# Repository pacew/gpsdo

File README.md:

<!-- -*- mode:gfm -*- -->

Documentation: https://pacew.github.io/gpsdo/

Schematic [PDF](schematic.pdf)

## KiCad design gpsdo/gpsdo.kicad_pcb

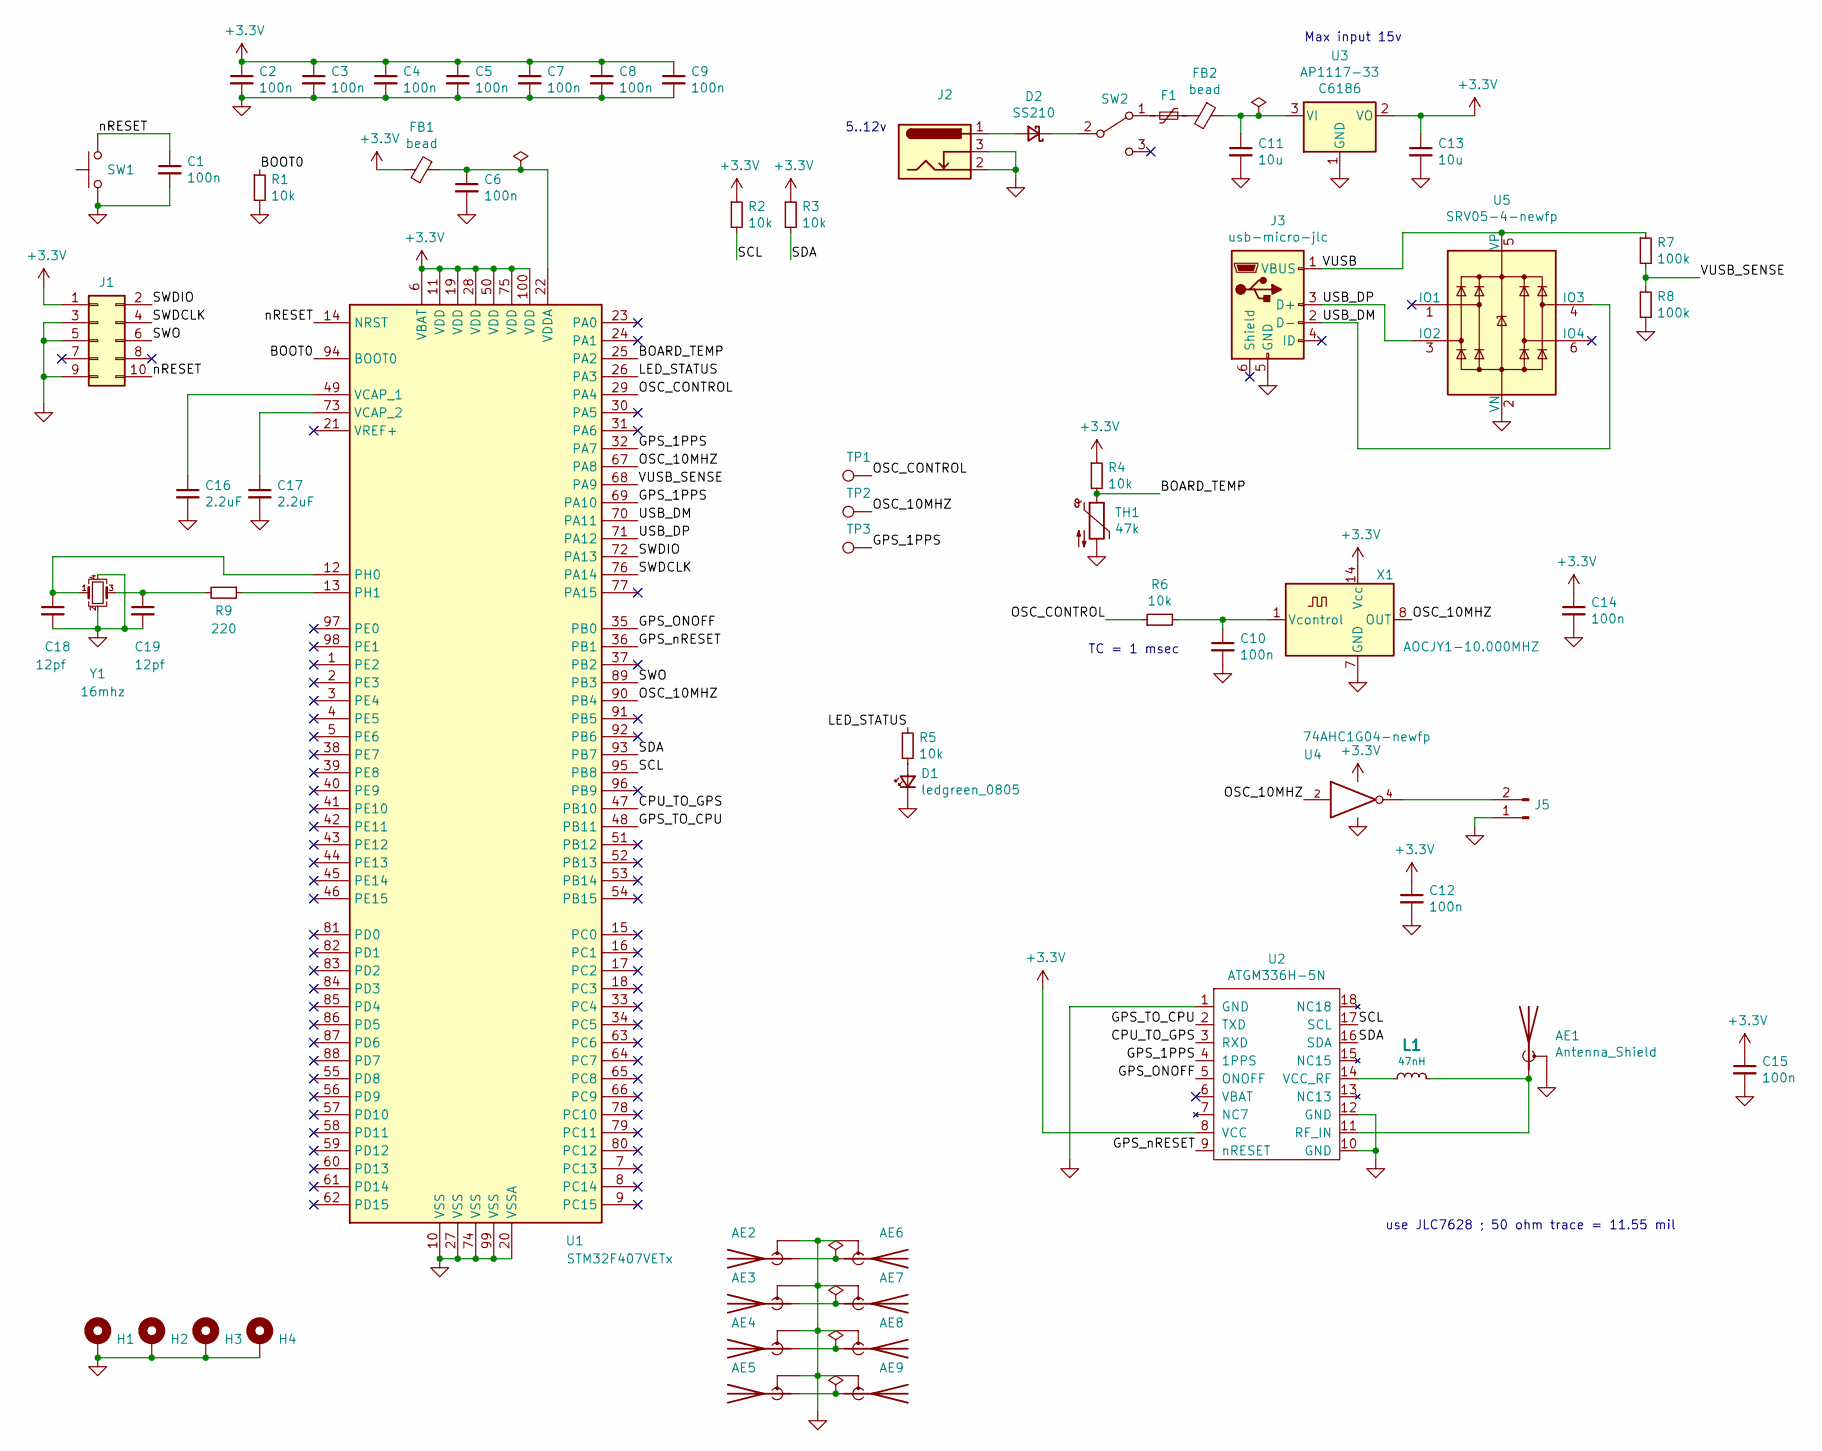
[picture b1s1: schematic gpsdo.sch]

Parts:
AE1, AE2, AE3, AE4, AE5, AE6, AE7, AE8, AE9: Antenna_Shield; sma
C1, C2, C3, C4, C5, C6, C7, C8, C9, C10, C12, C14, C15: 100n; C_0402_1005Metric; LCSC C1525
C11, C13: 10u; C_0402_1005Metric; LCSC C15525
C16, C17: 2.2uF; C_0603_1608Metric; LCSC C23630
C18, C19: 12pf; C_0402_1005Metric; LCSC C1547
D1: ledgreen_0805; LED_0805_2012Metric; LCSC C2297
D2: SS210; D_SMA; LCSC C14996
F1: fuse-250mA; Fuse_1206_3216Metric; LCSC C70068
FB1, FB2: bead; L_0805_2012Metric; LCSC C1015
H1, H2, H3, H4: MountingHole_Pad; MountingHole_3.2mm_M3_Pad
J1: Conn_02x05_Odd_Even; PinHeader_2x05_P1.27mm_Vertical
J2: Barrel_Jack_Switch; BarrelJack_Horizontal
J3: usb-micro-jlc; LCSC C404969
J5: Conn_01x02_Male; PinHeader_1x02_P2.54mm_Vertical
L1: 47nH; L_0603_1608Metric; LCSC C29683
R1, R2, R3, R4, R5, R6: 10k; R_0402_1005Metric; LCSC C25744
R7, R8: 100k; R_0402_1005Metric; LCSC C25741
R9: 220; R_0402_1005Metric; LCSC C25091
SW1: pushbutton_switch; SW_PUSH_6mm
SW2: SW_SPDT; Switch_Toggle_ATE1D-2M3-10-Z
TH1: 47k; R_0603_1608Metric; LCSC C86142
TP1, TP2, TP3: TestPoint; TestPoint_Pad_D1.0mm
U1: STM32F407VETx; LQFP-100_14x14mm_P0.5mm; lcsc C28730
U2: ATGM336H-5N; module18_9.7x10.1mm_P1.1mm; LCSC C90770
U3: AP1117-33; SOT-223-3_TabPin2; LCSC C6186
U4: 74AHC1G04-newfp; SOT-70-dck; LCSC C7466
U5: SRV05-4-newfp; SOT-23-6L-srv05; LCSC C85364
X1: AOCJY1-10.000MHZ; Oscillator_DIP-14
Y1: 16mhz; Crystal_SMD_3225-4Pin_3.2x2.5mm; LCSC C13738

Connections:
+3V3: C2.1, C3.1, C4.1, C5.1, C7.1, C8.1, C9.1, C12.1, C13.1, C14.1, C15.1, FB1.1, J1.1, R2.1, R3.1, R4.1, U1.6 (VBAT), U1.11 (VDD), U1.19 (VDD), U1.28 (VDD), U1.50 (VDD), U1.75 (VDD), U1.100 (VDD), U2.8 (VCC), U3.2 (VO), U4.5 (VCC), X1.14 (Vcc)
/BOARD_TEMP: R4.2, TH1.1, U1.25 (PA2)
/BOOT0: R1.1, U1.94 (BOOT0)
/CPU_TO_GPS: U1.47 (PB10), U2.3 (RXD)
/GPS_1PPS: TP3.1, U1.32 (PA7), U1.69 (PA10), U2.4 (1PPS)
/GPS_ONOFF: U1.35 (PB0), U2.5 (ONOFF)
/GPS_TO_CPU: U1.48 (PB11), U2.2 (TXD)
/GPS_nRESET: U1.36 (PB1), U2.9 (nRESET)
/LED_STATUS: R5.1, U1.26 (PA3)
/OSC_10MHZ: TP2.1, U1.67 (PA8), U1.90 (PB4), U4.2, X1.8 (OUT)
/OSC_CONTROL: R6.1, TP1.1, U1.29 (PA4)
/SCL: R2.2, U1.95 (PB8), U2.17 (SCL)
/SDA: R3.2, U1.93 (PB7), U2.16 (SDA)
/SWDCLK: J1.4, U1.76 (PA14)
/SWDIO: J1.2, U1.72 (PA13)
/SWO: J1.6, U1.89 (PB3)
/USB_DM: J3.2 (D-), U1.70 (PA11), U5.4 (IO3)
/USB_DP: J3.3 (D+), U1.71 (PA12), U5.3 (IO2)
/VUSB: J3.1 (VBUS), R7.1, U5.5 (VP)
/VUSB_SENSE: R7.2, R8.1, U1.68 (PA9)
/nRESET: C1.1, J1.10, SW1.2, U1.14 (NRST)
GND: AE1.2 (Shield), AE2.2 (Shield), AE3.2 (Shield), AE4.2 (Shield), AE5.2 (Shield), AE6.2 (Shield), AE7.2 (Shield), AE8.2 (Shield), AE9.2 (Shield), C1.2, C2.2, C3.2, C4.2, C5.2, C6.2, C7.2, C8.2, C9.2, C10.2, C11.2, C12.2, C13.2, C14.2, C15.2, C16.2, C17.2, C18.2, C19.2, D1.1 (K), H1.1, H2.1, H3.1, H4.1, J1.3, J1.5, J1.9, J2.2, J2.3, J3.5 (GND), J5.1, R1.2, R8.2, SW1.1, TH1.2, U1.10 (VSS), U1.20 (VSSA), U1.27 (VSS), U1.74 (VSS), U1.99 (VSS), U2.1 (GND), U2.10 (GND), U2.12 (GND), U3.1 (GND), U4.3 (GND), U5.2 (VN), X1.7 (GND), Y1.2, Y1.4
unnamed: AE1.1 (A), L1.2, U2.11 (RF_IN)
unnamed: AE2.1 (A), AE6.1 (A)
unnamed: AE3.1 (A), AE7.1 (A)
unnamed: AE4.1 (A), AE8.1 (A)
unnamed: AE5.1 (A), AE9.1 (A)
unnamed: C6.1, FB1.2, U1.22 (VDDA)
unnamed: C10.1, R6.2, X1.1 (Vcontrol)
unnamed: C11.1, FB2.1, U3.3 (VI)
unnamed: C16.1, U1.49 (VCAP_1)
unnamed: C17.1, U1.73 (VCAP_2)
unnamed: C18.1, U1.12 (PH0), Y1.1
unnamed: C19.1, R9.2, Y1.3
unnamed: D1.2 (A), R5.2
unnamed: D2.1 (K), SW2.2 (B)
unnamed: D2.2 (A), J2.1
unnamed: F1.1, FB2.2
unnamed: F1.2, SW2.1 (A)
unnamed: J5.2, U4.4
unnamed: L1.1, U2.14 (VCC_RF)
unnamed: R9.1, U1.13 (PH1)

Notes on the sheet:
TC = 1 msec
5..12v
Max input 15v
use JLC7628 ; 50 ohm trace = 11.55 mil

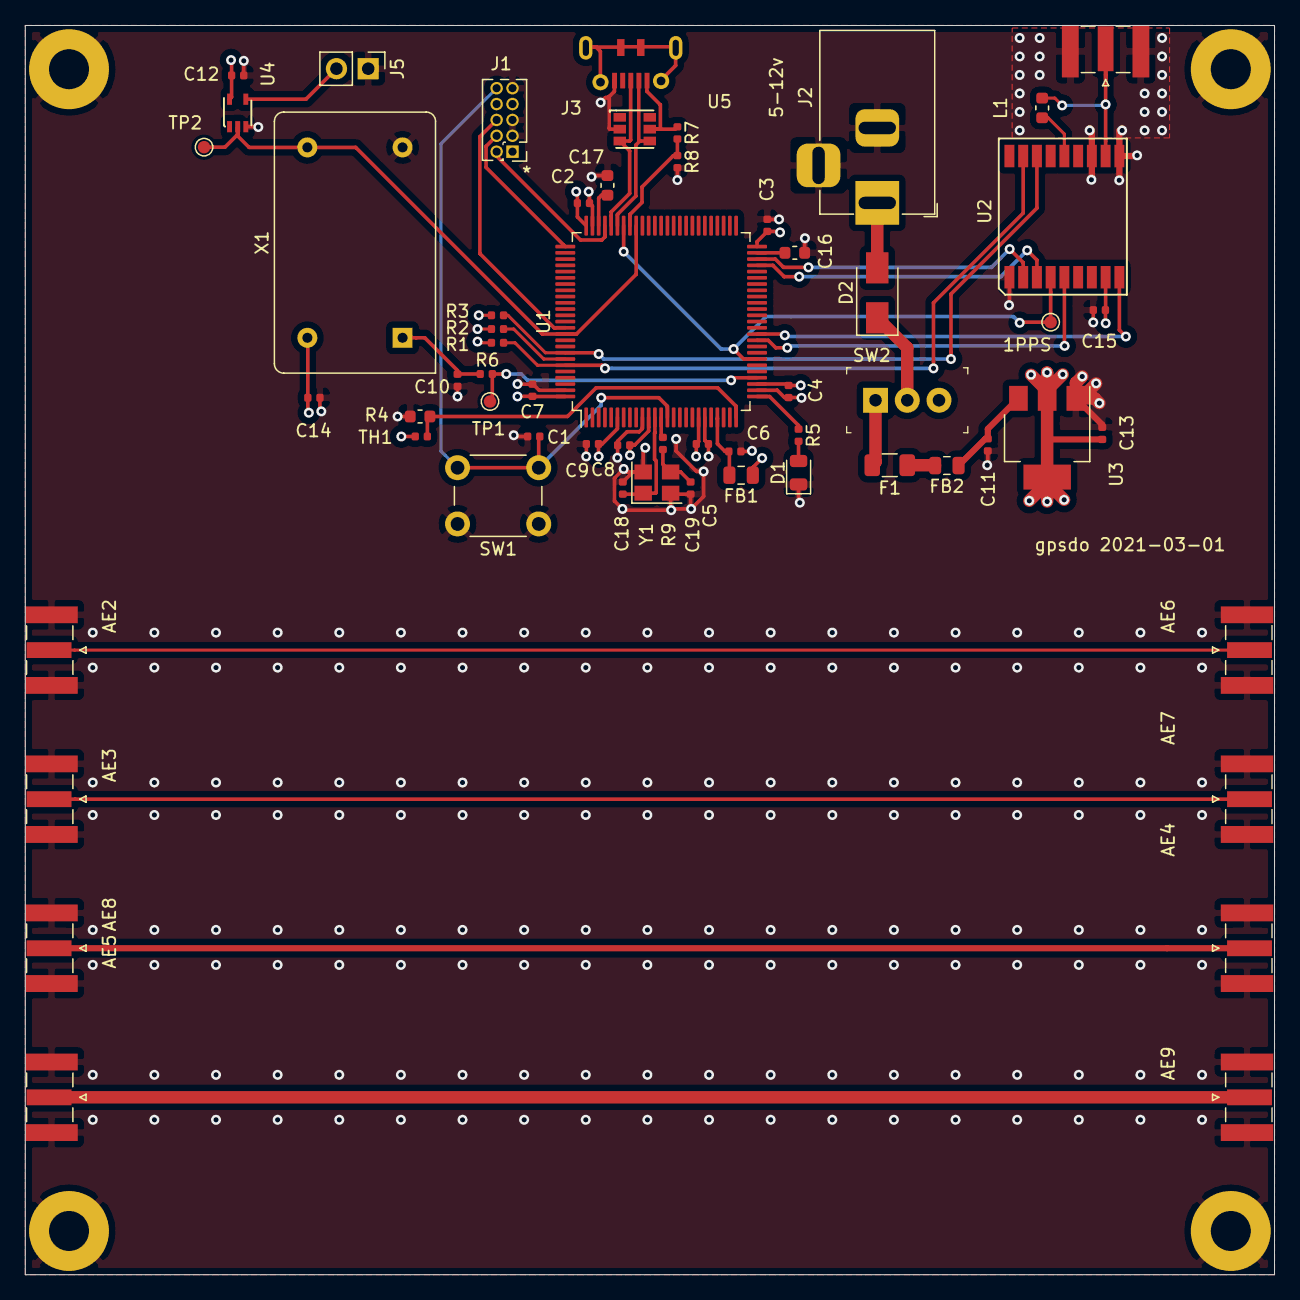
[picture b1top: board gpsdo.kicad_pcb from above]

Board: 4 copper layers, 100.0 x 100.0 mm, 64 parts (0 on the bottom side), 42 nets.

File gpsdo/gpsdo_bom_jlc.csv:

"Comment","Designator","Footprint","LCSC Part #"
"100n","C2,C3,C4,C5,C7,C8,C9,C1,C6,C12,C14,C15,C10","C_0402_1005Metric","C1525"
"10u","C11,C13","C_0402_1005Metric","C15525"
"2.2uF","C16,C17","C_0603_1608Metric","C23630"
"12pf","C18,C19","C_0402_1005Metric","C1547"
"ledgreen_0805","D1","LED_0805_2012Metric","C2297"
"SS210","D2","D_SMA","C14996"
"fuse-250mA","F1","Fuse_1206_3216Metric","C70068"
"bead","FB2,FB1","L_0805_2012Metric","C1015"
"usb-micro-jlc","J3","usb-micro-jlc","C404969"
"47nH","L1","L_0603_1608Metric","C29683"
"10k","R1,R5,R6,R4,R2,R3","R_0402_1005Metric","C25744"
"100k","R7,R8","R_0402_1005Metric","C25741"
"220","R9","R_0402_1005Metric","C25091"
"47k","TH1","R_0603_1608Metric","C86142"
"STM32F407VETx","U1","LQFP-100_14x14mm_P0.5mm","C28730"
"ATGM336H-5N","U2","module18_9.7x10.1mm_P1.1mm","C90770"
"AP1117-33","U3","SOT-223-3_TabPin2","C6186"
"74AHC1G04-newfp","U4","SOT-70-dck","C7466"
"SRV05-4-newfp","U5","SOT-23-6L-srv05","C85364"
"16mhz","Y1","Crystal_SMD_3225-4Pin_3.2x2.5mm","C13738"

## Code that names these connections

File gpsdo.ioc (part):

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PH0-OSC_IN.Signal=RCC_OSC_IN
Mcu.UserName=STM32F407VETx
PB10.Mode=Asynchronous
PA11.Mode=Device_Only
PB11.Signal=USART3_RX
RCC.SYSCLKSource=RCC_SYSCLKSOURCE_PLLCLK
PA12.Signal=USB_OTG_FS_DP
PC7.Signal=USART6_RX
PH0-OSC_IN.Mode=HSE-External-Clock-Source
RCC.HSE_VALUE=16000000
PB2.Signal=GPIO_Output
PB3.Mode=Trace_Asynchronous_SW
PA14.Mode=Trace_Asynchronous_SW
PB7.Signal=I2C1_SDA
PA8.Signal=S_TIM1_CH1
PH1-OSC_OUT.Mode=HSE-External-Clock-Source
Mcu.Package=LQFP100
PB1.Signal=GPIO_Output
PA10.Signal=S_TIM1_CH3
PB4.Signal=S_TIM3_CH1
PA3.Signal=GPIO_Output
PC6.Signal=USART6_TX
PA0-WKUP.Signal=ADCx_IN0
PA13.Signal=SYS_JTMS-SWDIO
PA9.Mode=Activate_VBUS
PB11.Mode=Asynchronous
PC6.Mode=Asynchronous
PA9.Signal=USB_OTG_FS_VBUS
PE11.Signal=S_TIM1_CH2
PA1.Signal=ADCx_IN1
PB10.Signal=USART3_TX
PA5.Signal=COMP_DAC2_group
board=custom
PH1-OSC_OUT.Signal=RCC_OSC_OUT
PA13.Mode=Trace_Asynchronous_SW
Mcu.Name=STM32F407V(E-G)Tx
PA2.Signal=ADCx_IN2
PB3.Signal=SYS_JTDO-SWO
PA4.Signal=COMP_DAC1_group
RCC.SYSCLKFreq_VALUE=168000000
PA12.Mode=Device_Only
PB7.Mode=I2C
PA11.Signal=USB_OTG_FS_DM
PA14.Signal=SYS_JTCK-SWCLK
PB8.Mode=I2C
PB8.Signal=I2C1_SCL
PC7.Mode=Asynchronous
PB0.Signal=GPIO_Output
PA7.Signal=S_TIM3_CH2

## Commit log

2021-02-25 start
2021-02-25 main
2021-02-26 layout
2021-02-28 makefile
2021-02-28 rotate
2021-02-28 usb connector
2021-03-02 order
2021-03-18 blink
2021-03-18 cleanup
2021-03-19 clock
2021-03-19 docs
2021-03-21 init
2021-03-23 foothold
2021-03-23 swocat
2021-03-24 speedup
2021-03-24 printf
2021-03-24 uart
2021-03-28 gpsmon
2021-03-30 tim1
2021-04-01 graphs
2021-04-01 tim2
2021-04-03 libje
2021-04-03 test
2021-04-03 pages
2021-04-03 text
2021-04-03 link
2021-04-03 Set theme jekyll-theme-slate
2021-04-05 regs
2021-04-05 new regs
